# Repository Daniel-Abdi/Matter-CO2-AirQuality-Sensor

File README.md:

## Author: Daniel Abdi

# Introduction

This repo contains code and design files for building your own Matter-based CO2 air quality monitor. The design is based on an ESP32-C6 and SCD40 CO2 sensor, though you can probably replace the SCD40 with any of its cousins in the SCD4x family. It's capable of measuring CO2 in PPM, relative humidity, and the current temperature. Though I only make use of the CO2 measurement in this code. Modifications to add in that functionality are left as an excercise for the reader 😁.  Please note that I'm using ESP-IDF v5.4 and esp-matter at release/v1.4 when compiling. Also note that my code is frankly quite messy and it's doubtful that it adheres to best practices for setting these attributes. Might be worth it to fix later, but this whole project has been more for a fun excercise than anything else. 

I don't have 3D models of the C6 or the SCD40 so you'll have to use your imagination for those 😆

# How to use it

I make use of a custom board that I designed specifically for this project, so if you'd like to follow my example, you would either have to order a set of boards using the included KiCAD design files, or set up your own example using an ESP32-C6 devkit and a SCD4X breakout board. If you choose to go with your own solution, make sure you change the I2C pins set up within the Sensirion driver folder. I'm going to assume you're somewhat familiar with Matter, esp-matter, ESP-IDF, and KiCAD. Regardless, you should just be able to compile, flash, and pair using a Matter controller you have nearby (I use an Aeotec smart hub).

### Caution with ESP-Matter
 You should also note that depending on which commit of esp-matter you're using, you may run into issues using esp-matter to set the Air Quality value of the Air Quality cluster that is mandatory for the device. Currently, this cluster has a flag of `MANAGED_INTERNALLY`, which means that you need to use the underlying Attribute Accessor Interface (AAI) to set it. That's why those other air-quality-sensor-manager files are included in the repository. Those files are pulled straight from the example in the CHIP repository. If you find that you see an error message where you can't set the value of that attribute using the esp-matter APIs, uncomment the lines in app_main.cpp that represent AAI, and use those functions instead. You can still use esp-matter to set the CO2 concentration. There is also a patch [here](https://github.com/espressif/esp-matter/issues/1548) that you can try and use as well. This should remove that flag and allow you to use esp-matter. You will also need to enable the Air Quality and Carbon Dioxide Concentration clusters in menuconfig for esp-matter. 

### Pairing
To pair, please use the information at the esp-matter [docs](https://docs.espressif.com/projects/esp-matter/en/latest/esp32/developing.html#building-a-color-temperature-lightbulb). You can use the QR code there to pair to any esp-matter device you create. I've also included the pairing code here for your use.

Here's what it'll look like after pairing:

# The Details

The main components of this project are the SCD4X drivers from Sensirion, included in the `/drivers` directory, and `app_main.cpp`, which contains all the code that we really care about. The Sensiron drivers are cloned from  [Here (Github)](https://github.com/Sensirion/embedded-i2c-scd4x/tree/master), with some modifications from my side to work with my custom code (basically adding in the I2C implementation and setting the right pins). I've also included some code from the CHIP repository that represents a way to access attributes using the Attribute Accessor Interface (AAI). Read above on when you might need to use this code, otherwise you can feel free to leave it alone. 

### Clusters
Currently, the device contains 2 clusters of importance to us: The Air Quality cluster, which is mandatory for an Air Quality device, and the CO2 concentration cluster. I've also added the CO2 concentration feature flag, instead of using a level-approach (Like a bad-moderate-good-etc scale) read more in the cluster definitions from the CSA to understand these feature flags and which might work for your use case. Upon commissioning into the Matter fabric, these values are updated every ~5 seconds. SmartThings will be helpful and show you an hourly average of the readings going back 24 hours, so you can see how the CO2 in a space changes over the course of a day or so, even when you aren't looking at the app.

 If you make a change to the features or clusters on the device, make sure to erase-flash, delete from your Matter app, and re-pair, otherwise they may not show up. 

### Using Thread
If you have a Thread border router, you can also enable Thread support and use Matter over Thread with the C6. I haven't done that because I'm not sure if my controller supports Thread and frankly in my use case it doesn't matter as it'd be the only Thread device on the network anyways. 

If you have any questions about my implementation or need help setting up your own, feel free to open an issue and I will try and help.

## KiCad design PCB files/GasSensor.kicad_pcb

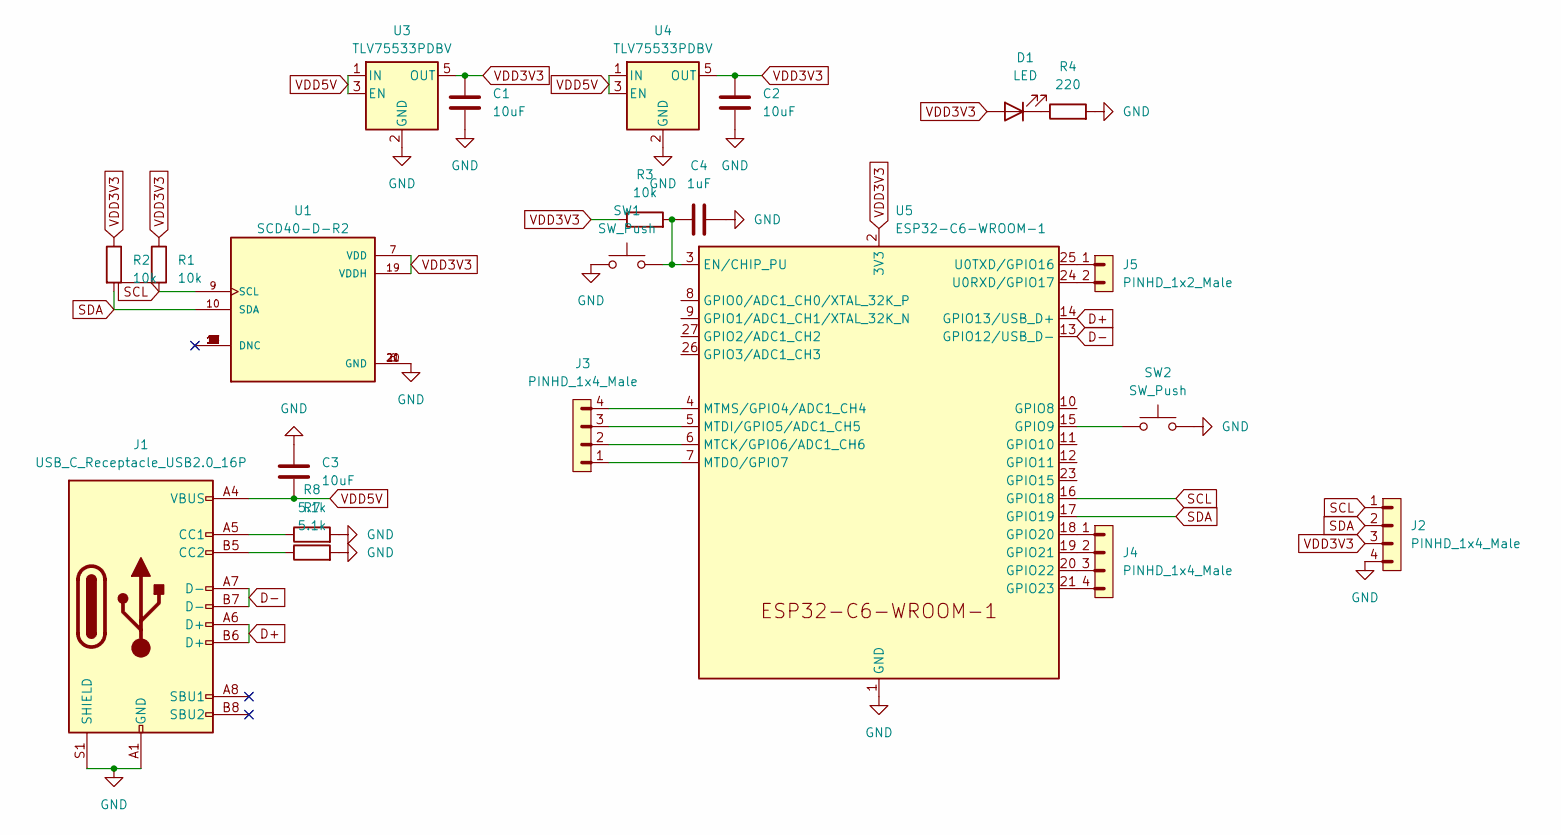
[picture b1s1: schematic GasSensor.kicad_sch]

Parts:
C1, C2, C3: 10uF; C_1206_3216Metric
C4: 1uF; C_1206_3216Metric
D1: LED; LED_0805_2012Metric
J1: USB_C_Receptacle_USB2.0_16P; USB_C_Receptacle_G-Switch_GT-USB-7010ASV
J2, J3, J4: PINHD_1x4_Male; PinHeader_1x04_P2.54mm_Vertical
J5: PINHD_1x2_Male; PinHeader_1x02_P2.54mm_Vertical
R1, R2, R3: 10k; R_1206_3216Metric
R4: 220; R_1206_3216Metric
R7, R8: 5.1k; R_1206_3216Metric
SW1, SW2: SW_Push; SW_Tactile_SPST_NO_Straight_CK_PTS636Sx25SMTRLFS
U1: SCD40-D-R2; XDCR_SCD40-D-R2; PARTREV 1.2
U3, U4: TLV75533PDBV; SOT-23-5
U5: ESP32-C6-WROOM-1

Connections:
D+: J1.A6 (D+), J1.B6 (D+), U5.14 (GPIO13/USB_D+)
D-: J1.A7 (D-), J1.B7 (D-), U5.13 (GPIO12/USB_D-)
GND: C1.2, C2.2, C3.1, C4.2, J1.A1 (GND), J1.A12 (GND), J1.B1 (GND), J1.B12 (GND), J1.S1 (SHIELD), J2.4, R4.2, R7.2, R8.2, SW1.1, SW2.2, U1.6 (GND), U1.20 (GND), U1.21 (GND), U3.2 (GND), U4.2 (GND), U5.1 (GND), U5.28 (GND), U5.29 (GND)
unnamed: D1.1 (K), R4.1
unnamed: J1.A5 (CC1), R8.1
unnamed: J1.B5 (CC2), R7.1
unnamed: C4.1, R3.2, SW1.2, U5.3 (EN/CHIP_PU)
unnamed: SW2.1, U5.15 (GPIO9)
unnamed: J4.1, U5.18 (GPIO20)
unnamed: J4.2, U5.19 (GPIO21)
unnamed: J4.3, U5.20 (GPIO22)
unnamed: J4.4, U5.21 (GPIO23)
unnamed: J3.2, U5.6 (MTCK/GPIO6/ADC1_CH6)
unnamed: J3.3, U5.5 (MTDI/GPIO5/ADC1_CH5)
unnamed: J3.1, U5.7 (MTDO/GPIO7)
unnamed: J3.4, U5.4 (MTMS/GPIO4/ADC1_CH4)
unnamed: J5.2, U5.24 (U0RXD/GPIO17)
unnamed: J5.1, U5.25 (U0TXD/GPIO16)
SCL: J2.1, R1.2, U1.9 (SCL), U5.16 (GPIO18)
SDA: J2.2, R2.2, U1.10 (SDA), U5.17 (GPIO19)
VDD3V3: C1.1, C2.1, D1.2 (A), J2.3, R1.1, R2.1, R3.1, U1.7 (VDD), U1.19 (VDDH), U3.5 (OUT), U4.5 (OUT), U5.2 (3V3)
VDD5V: C3.2, J1.A4 (VBUS), J1.A9 (VBUS), J1.B4 (VBUS), J1.B9 (VBUS), U3.1 (IN), U3.3 (EN), U4.1 (IN), U4.3 (EN)

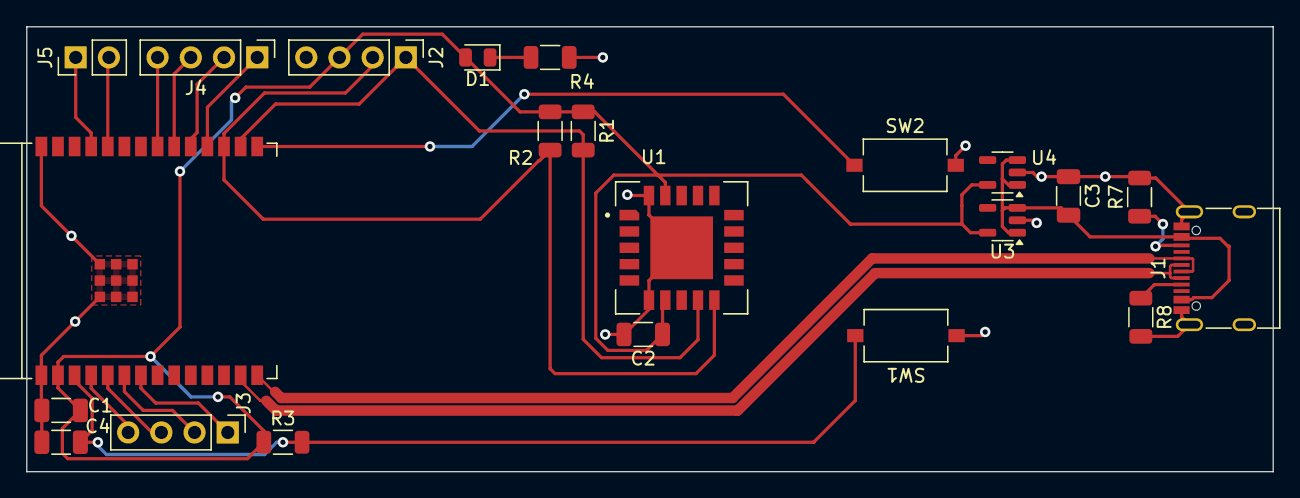
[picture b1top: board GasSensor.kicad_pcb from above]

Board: 2 copper layers, 95.3 x 34.0 mm, 22 parts (0 on the bottom side), 22 nets.

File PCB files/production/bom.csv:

Designator,Footprint,Quantity,Value,LCSC Part #
"C1, C2, C3",1206,3,10uF,
C4,1206,1,1uF,
D1,0805,1,LED,
J1,USB_C_Receptacle_G-Switch_GT-USB-7010ASV,1,USB_C_Receptacle_USB2.0_16P,
"J2, J3, J4",PinHeader_1x04_P2.54mm_Vertical,3,PINHD_1x4_Male,
J5,PinHeader_1x02_P2.54mm_Vertical,1,PINHD_1x2_Male,
"R1, R2, R3",1206,3,10k,
R4,1206,1,220,
"R7, R8",1206,2,5.1k,
"SW1, SW2",SW_Tactile_SPST_NO_Straight_CK_PTS636Sx25SMTRLFS,2,SW_Push,
U1,XDCR_SCD40-D-R2,1,SCD40-D-R2,
"U3, U4",SOT-23-5,2,TLV75533PDBV,
U5,ESP32-C6-WROOM-1,1,ESP32-C6-WROOM-1,

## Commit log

2025-10-19 First commit, pushing all my files into the repo.
2025-10-19 Removed the TOC setting that apparently doesn't render right on github?? That's kind of ridiculous...
2025-10-20 Updated the README to look less terrible.
2025-10-20 Updated images to not be so huge
2025-10-20 Scaled properly this time????
2025-10-20 Rearranged some text.
